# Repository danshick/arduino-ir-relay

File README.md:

arduino-ir-relay
---

Kicad
---
Kicad files for schematic, PCB, footprints, and gerber/drill files for the project

PlatformIO
---
code folder contains PlatformIO project for compatible arduino code

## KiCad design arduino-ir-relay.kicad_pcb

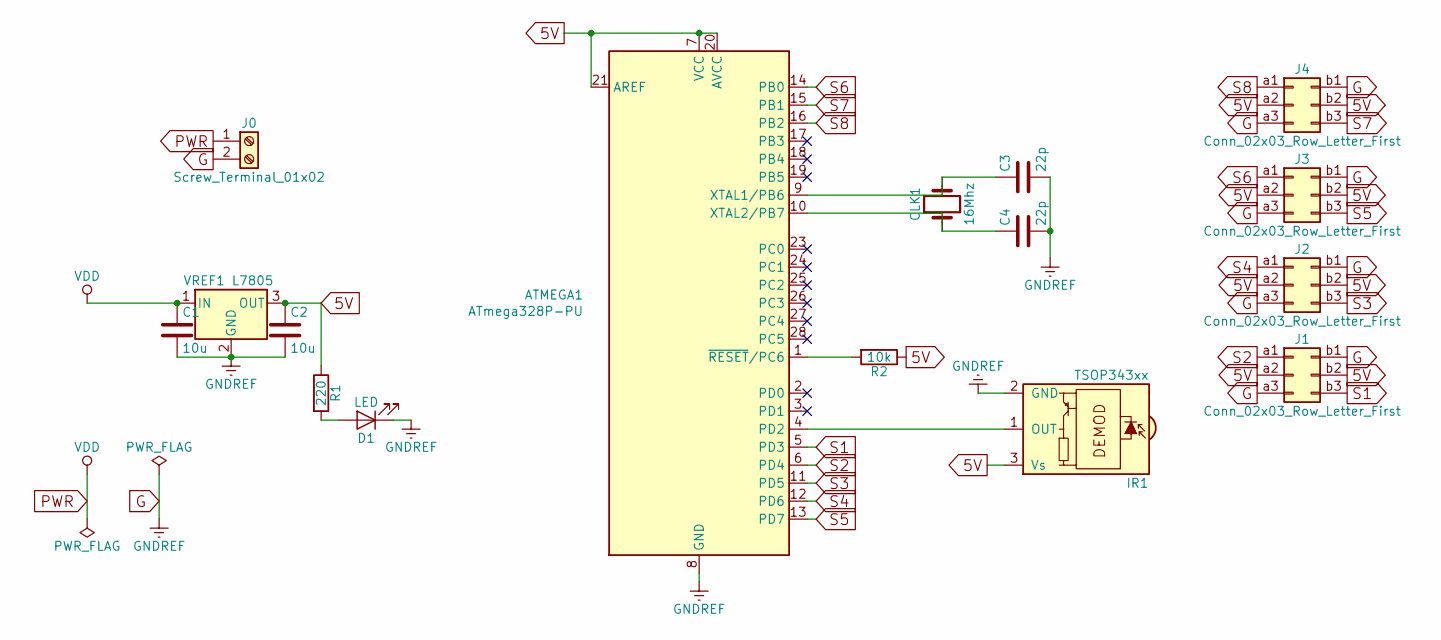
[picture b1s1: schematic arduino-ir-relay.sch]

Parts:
ATMEGA1: ATmega328P-PU; DIP-28_W7.62mm
C1, C2: 10u; C_Disc_D3.0mm_W1.6mm_P2.50mm
C3, C4: 22p; C_Disc_D3.0mm_W1.6mm_P2.50mm
CLK1: 16Mhz; Crystal_HC49-U_Vertical
D1: LED; LED_D5.0mm
IR1: TSOP343xx; Vishay_MOLD-3Pin
J0: Screw_Terminal_01x02; TerminalBlock_RND_205-00067_1x02_P7.50mm_Horizontal
J1, J2, J3, J4: Conn_02x03_Row_Letter_First; Pin_Header_Straight_2x03_Pitch2.54mm
R1: 220; R_Axial_DIN0204_L3.6mm_D1.6mm_P5.08mm_Horizontal
R2: 10k; R_Axial_DIN0204_L3.6mm_D1.6mm_P5.08mm_Horizontal
VREF1: L7805; TO-220-3_Vertical

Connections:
5V: ATMEGA1.7 (VCC), ATMEGA1.20 (AVCC), ATMEGA1.21 (AREF), C2.1, IR1.3 (Vs), J1.a2, J1.b2, J2.a2, J2.b2, J3.a2, J3.b2, J4.a2, J4.b2, R1.1, R2.1, VREF1.3 (OUT)
G: ATMEGA1.8 (GND), ATMEGA1.22 (GND), C1.2, C2.2, C3.2, C4.2, D1.1 (K), IR1.2 (GND), J0.2, J1.a3, J1.b1, J2.a3, J2.b1, J3.a3, J3.b1, J4.a3, J4.b1, VREF1.2 (GND)
unnamed: ATMEGA1.1 (~RESET~/PC6), R2.2
unnamed: ATMEGA1.4 (PD2), IR1.1 (OUT)
unnamed: ATMEGA1.9 (XTAL1/PB6), C3.1, CLK1.2
unnamed: ATMEGA1.10 (XTAL2/PB7), C4.1, CLK1.1
unnamed: D1.2 (A), R1.2
PWR: C1.1, J0.1, VREF1.1 (IN)
S1: ATMEGA1.5 (PD3), J1.b3
S2: ATMEGA1.6 (PD4), J1.a1
S3: ATMEGA1.11 (PD5), J2.b3
S4: ATMEGA1.12 (PD6), J2.a1
S5: ATMEGA1.13 (PD7), J3.b3
S6: ATMEGA1.14 (PB0), J3.a1
S7: ATMEGA1.15 (PB1), J4.b3
S8: ATMEGA1.16 (PB2), J4.a1

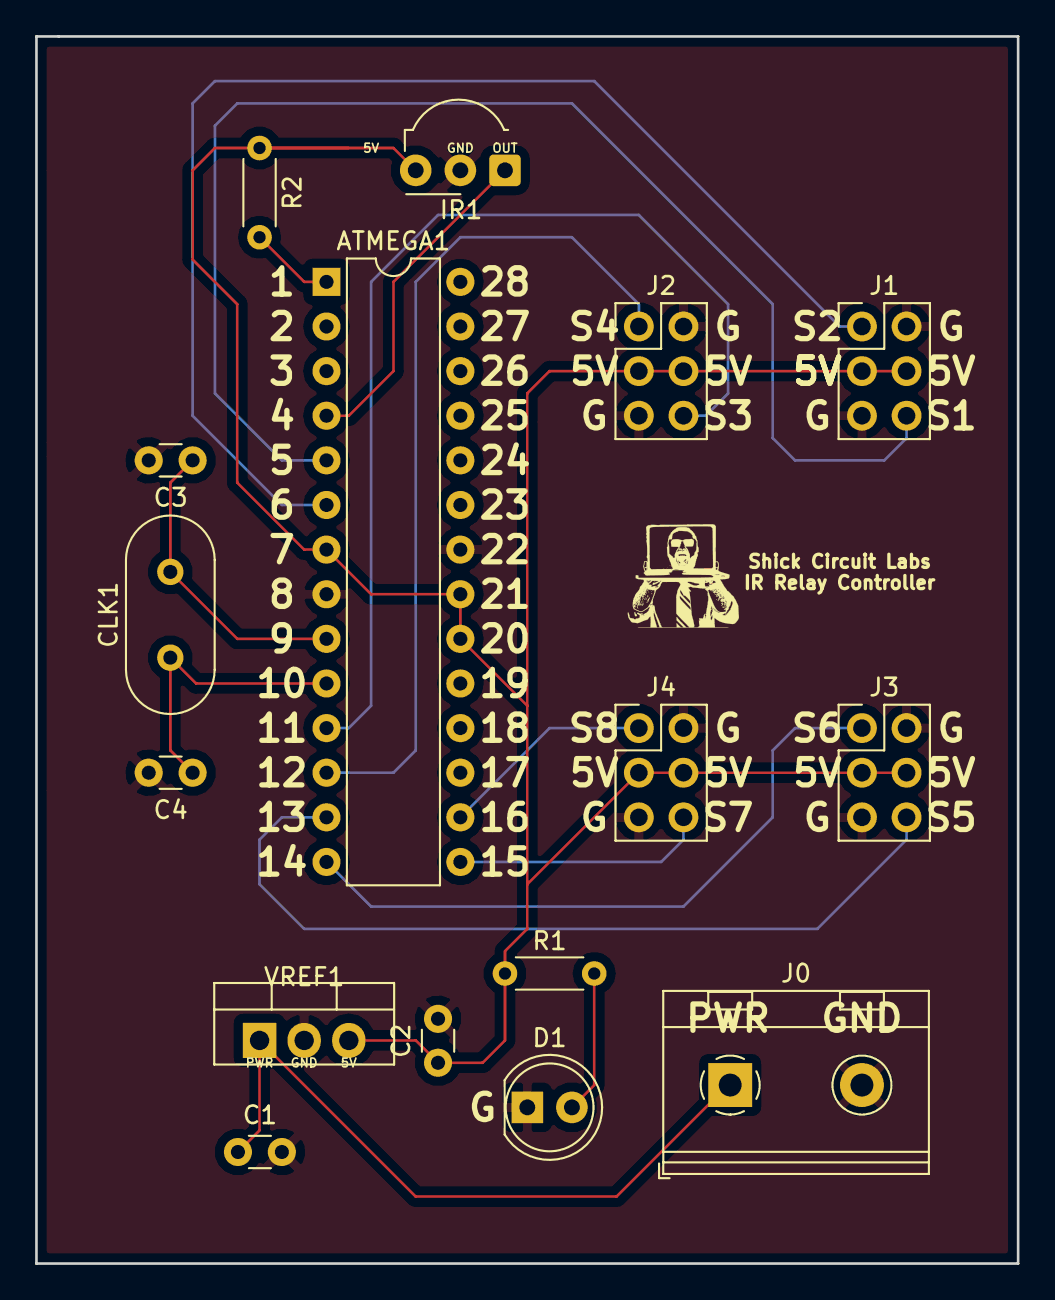
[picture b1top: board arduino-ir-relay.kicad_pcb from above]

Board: 2 copper layers, 55.9 x 69.9 mm, 16 parts (0 on the bottom side), 16 nets.

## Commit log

2018-07-22 Initial commit, kicad files and code
2018-07-22 Updated README.md with images of pcb
2019-03-13 Updated for Kicad 5
